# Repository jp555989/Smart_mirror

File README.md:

# Smart_mirror
This is a PCB board made in KiCad for a project called "Smart mirror", it's main task is controlling RGB LEDs via potentiometers, potentiometers should be connected to screw terminals with corresponding names (potentiometer_r,potentiometer_g,potentiometer_b). 

This board is powered by 12V.

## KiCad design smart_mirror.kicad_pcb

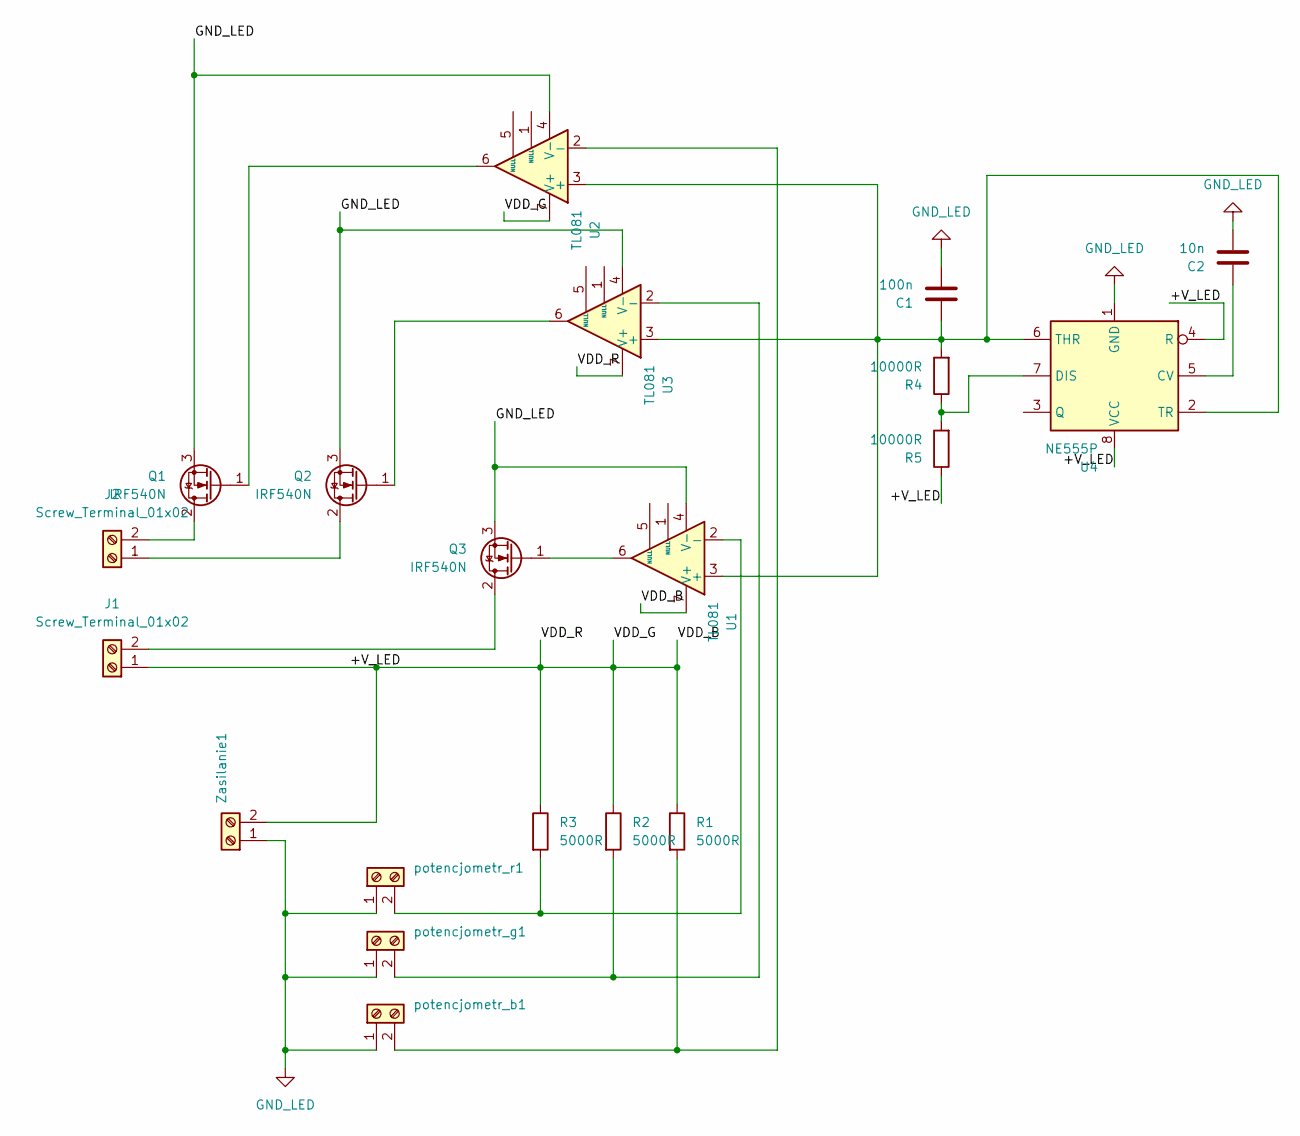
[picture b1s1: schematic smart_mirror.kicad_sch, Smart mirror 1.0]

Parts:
C1: 100n; C_0805_2012Metric_Pad1.18x1.45mm_HandSolder
C2: 10n; C_0805_2012Metric_Pad1.18x1.45mm_HandSolder
J1, J2: Screw_Terminal_01x02; TerminalBlock_MaiXu_MX126-5.0-02P_1x02_P5.00mm_wiekszepady
Q1, Q2, Q3: IRF540N; TO-220-3_Vertical_wiekszepady
R1, R2, R3: 5000R; R_0805_2012Metric
R4, R5: 10000R; R_0805_2012Metric_Pad1.20x1.40mm_HandSolder
U1, U2, U3: TL081; DIP794W45P254L959H508Q8_wiekszepady
U4: NE555P; DIP-8_W7.62mm_wiekszepady
Zasilanie1: Screw_Terminal_01x02; TerminalBlock_MaiXu_MX126-5.0-02P_1x02_P5.00mm_wiekszepady
potencjometr_b1: Screw_Terminal_01x02; TerminalBlock_MaiXu_MX126-5.0-02P_1x02_P5.00mm_wiekszepady
potencjometr_g1: Screw_Terminal_01x02; TerminalBlock_MaiXu_MX126-5.0-02P_1x02_P5.00mm_wiekszepady
potencjometr_r1: Screw_Terminal_01x02; TerminalBlock_MaiXu_MX126-5.0-02P_1x02_P5.00mm_wiekszepady

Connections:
/+V_LED: J1.1, R1.1, R2.1, R3.1, R5.1, U1.7 (V+), U2.7 (V+), U3.7 (V+), U4.4 (R), U4.8 (VCC), Zasilanie1.2
GND_LED: C1.2, C2.2, Q1.3 (S), Q2.3 (S), Q3.3 (S), U1.4 (V-), U2.4 (V-), U3.4 (V-), U4.1 (GND), Zasilanie1.1, potencjometr_b1.1, potencjometr_g1.1, potencjometr_r1.1
unnamed: J1.2, Q3.2 (D)
unnamed: J2.1, Q2.2 (D)
unnamed: J2.2, Q1.2 (D)
unnamed: Q1.1 (G), U2.6
unnamed: Q2.1 (G), U3.6
unnamed: Q3.1 (G), U1.6
unnamed: C1.1, R4.2, U1.3 (+), U2.3 (+), U3.3 (+), U4.2 (TR), U4.6 (THR)
unnamed: R3.2, U1.2 (-), potencjometr_r1.2
unnamed: R1.2, U2.2 (-), potencjometr_b1.2
unnamed: R2.2, U3.2 (-), potencjometr_g1.2
unnamed: C2.1, U4.5 (CV)
unnamed: R4.1, R5.2, U4.7 (DIS)

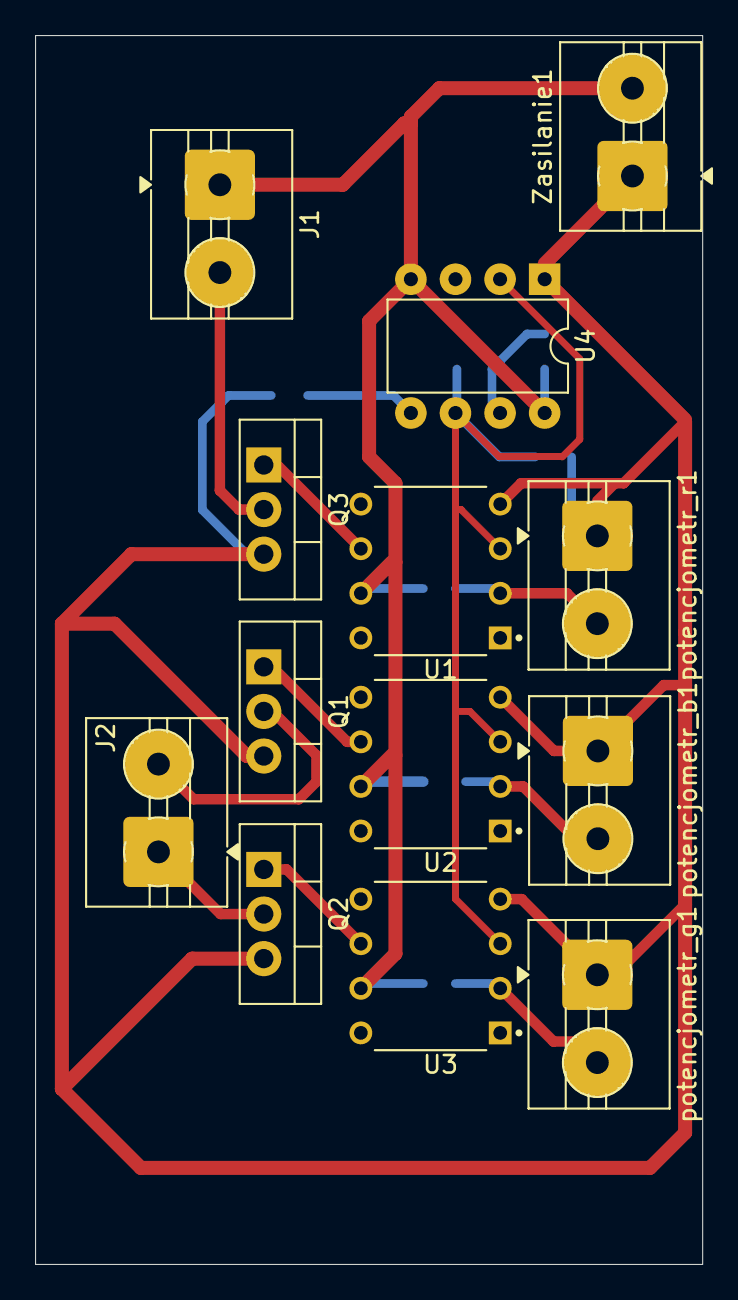
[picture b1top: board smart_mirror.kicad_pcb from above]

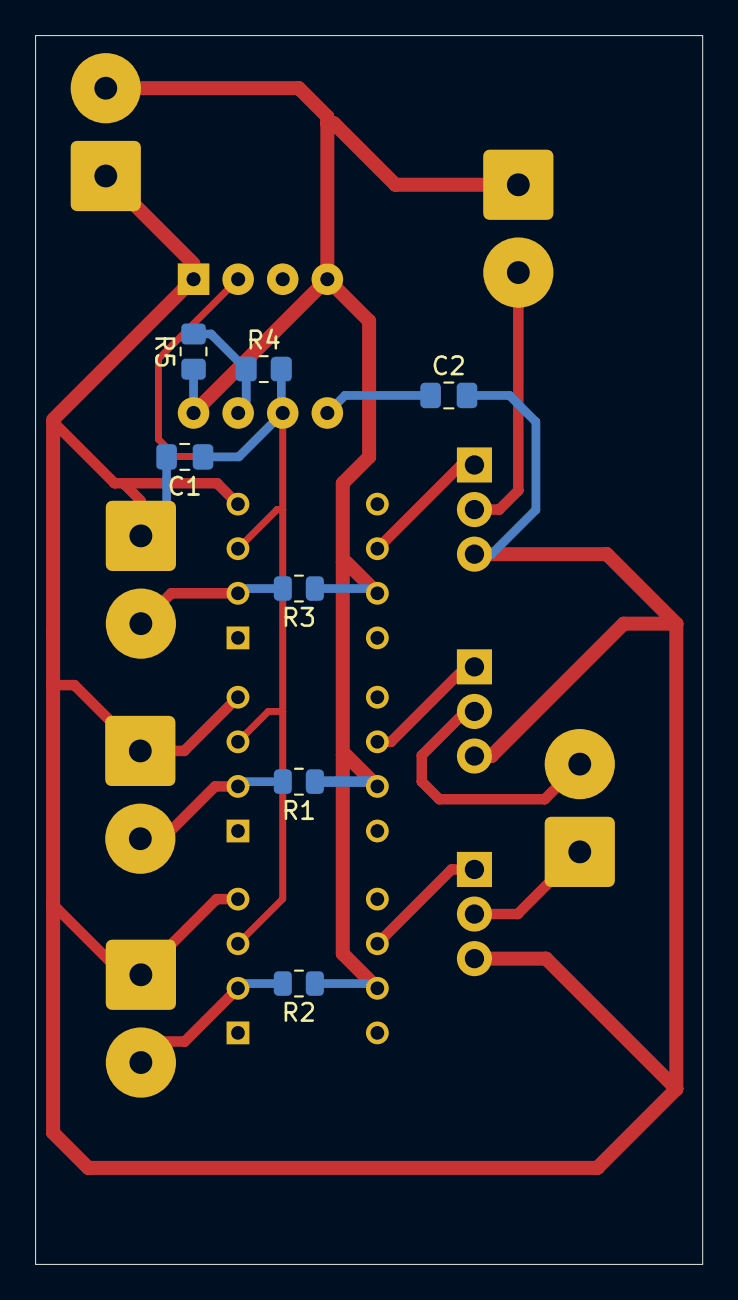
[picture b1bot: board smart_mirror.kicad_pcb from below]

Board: 2 copper layers, 38.0 x 70.0 mm, 20 parts (7 on the bottom side), 14 nets.
